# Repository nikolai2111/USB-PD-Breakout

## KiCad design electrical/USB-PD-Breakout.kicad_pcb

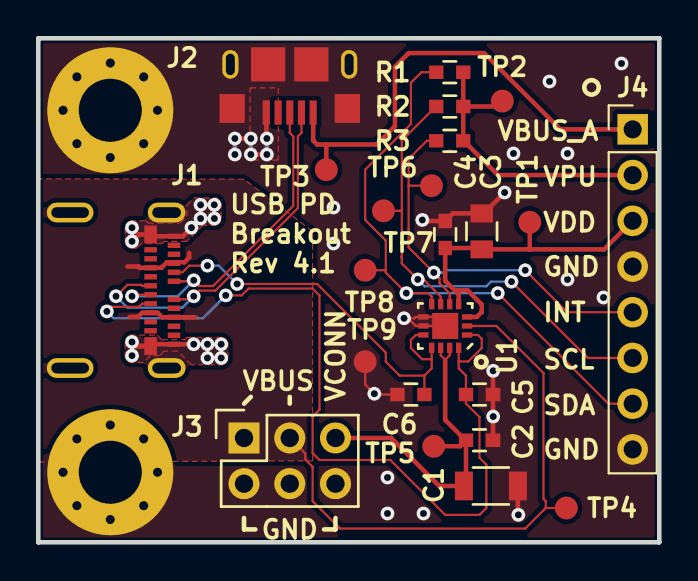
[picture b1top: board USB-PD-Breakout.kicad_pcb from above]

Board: 2 copper layers, 34.5 x 28.0 mm, 25 parts (0 on the bottom side), 13 nets.

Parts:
C1: 10uF; C_1206
C2, C4: 0.1uF; C_0603
C3: 1uF; C_0805
C5, C6: 470pF; C_0603
J1: USB-C_Female; USB-C_Female_105450-0101
J2: USB_OTG; USB_Micro-B_10118193
J3: CONN_02X03; Socket_Strip_Straight_2x03
J4: Conn_01x08_Male; Socket_Strip_Straight_1x08_Pitch2.54mm
R1, R2, R3: 4.7k; C_0603
TP1, TP2, TP3, TP4, TP5, TP6, TP7, TP8, TP9: TEST_1P; TP
U1: FUSB302BMPX; MLP_14
X1, X2: MTHOLE; MountingHole_3.5mm_Pad_Via

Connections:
/SCL: J4.6, R2.2, TP7.1, U1.6
/SDA: J4.7, R1.2, TP8.1, U1.7
/USB20_D+: J1.A6, J1.B6, J2.3
/USB20_D-: J1.A7, J1.B7, J2.2
/USBC_CC1: C6.1, J1.A5, U1.10, U1.11
/USBC_CC2: C5.1, J1.B5, U1.1, U1.14
/~INT: J4.5, R3.2, TP6.1, U1.5
GND: C1.2, C2.2, C3.2, C4.2, C5.2, C6.2, J1.A1, J1.A12, J1.B1, J1.B12, J1.SHLD, J2.5, J2.6, J2.7, J2.8, J2.9, J2.10, J3.2, J3.4, J3.6, J4.4, J4.8, TP9.1, U1.8, U1.9, U1.15, X1.1, X2.1
VBUS_A: J2.1, J4.1, TP3.1
VBUS_C: J1.A4, J1.A9, J1.B4, J1.B9, J3.1, J3.3, TP4.1, U1.2
VCONN: C1.1, C2.1, J3.5, TP5.1, U1.12, U1.13
VDD: C3.1, C4.1, J4.3, TP1.1, U1.3, U1.4
V_PULLUP: J4.2, R1.1, R2.1, R3.1, TP2.1

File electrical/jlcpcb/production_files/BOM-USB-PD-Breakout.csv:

Comment,Designator,Footprint,LCSC
470pF,"C5,C6",C_0603,C107092
FUSB302BMPX,U1,MLP_14,C132291
USB_OTG,J2,USB_Micro-B_10118193,C132562
USB-C_Female,J1,USB-C_Female_105450-0101,C134092
0.1uF,"C2,C4",C_0603,C1591
CONN_02X03,J3,Socket_Strip_Straight_2x03,C236051
1uF,C3,C_0805,C24123
10uF,C1,C_1206,C9807
4.7k,"R1,R2,R3",C_0603,C99782

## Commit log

2023-04-15 Mod: Project so it could be easy ordered over JLCPCB
2023-04-16 Bug: Fixed the non existing holes in the USB footprints Mod: Changed the planes (GND and VBUS) from thermal relief to solid
